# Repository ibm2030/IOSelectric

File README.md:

IOSelectric
===========

Arduino based serial interface for an IBM I/O Selectric typewriter/printer

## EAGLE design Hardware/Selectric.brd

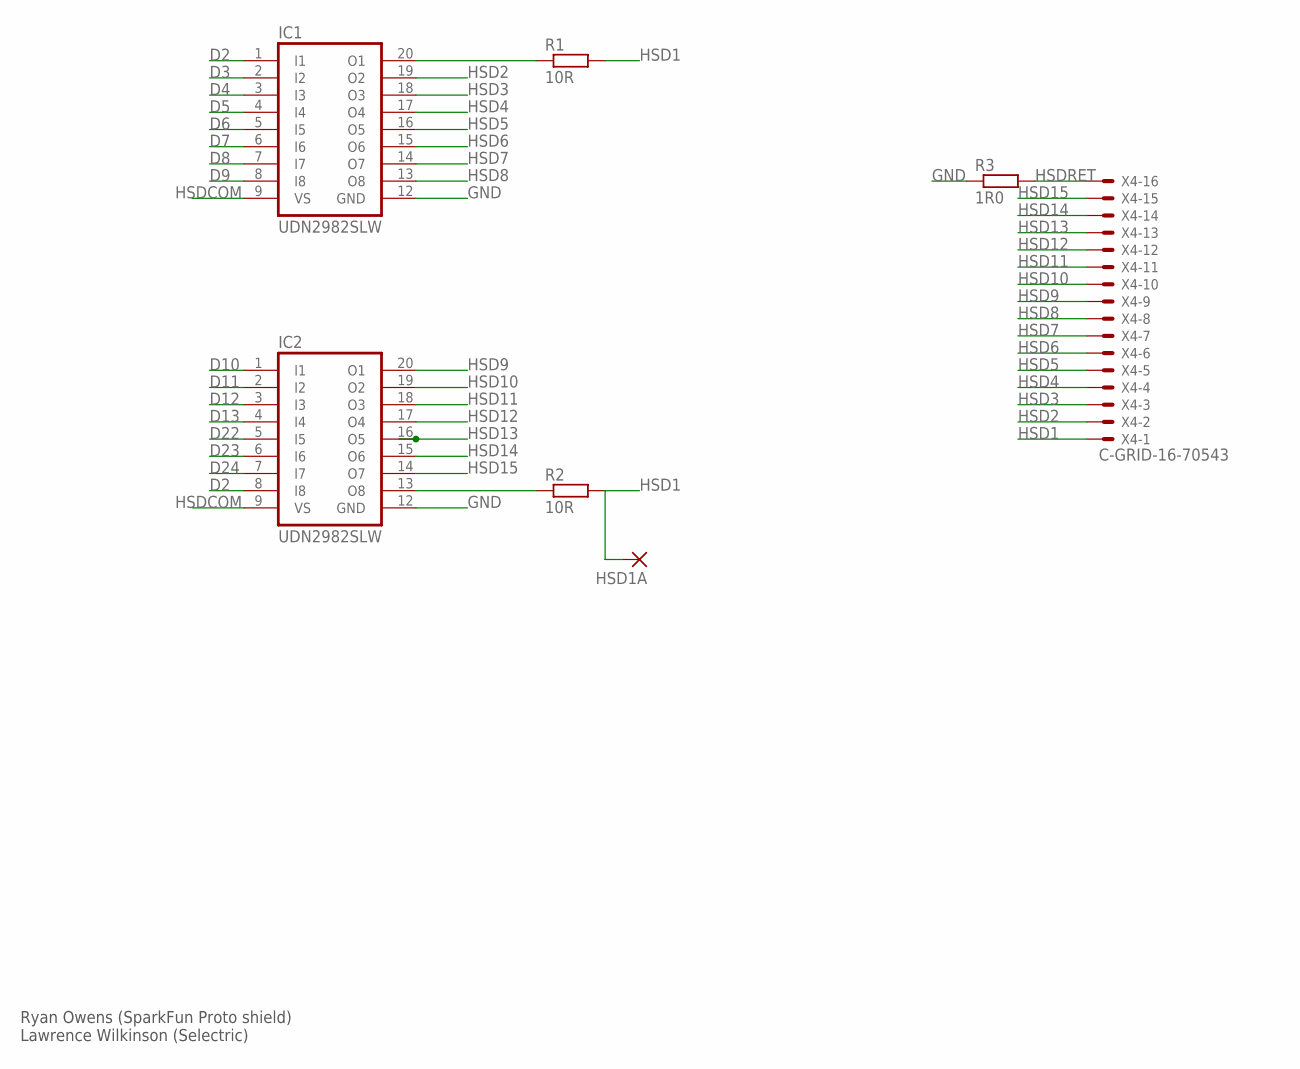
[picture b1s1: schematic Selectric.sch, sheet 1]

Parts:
HSD1A: 2,15/1,0
IC1, IC2: UDN2982SLW; SO20W; MPN UDN2982SLW
R1, R2: 10R; M1206
R3: 1R0; 0922/22
X4: C-GRID-16-70543; 70543-16

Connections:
D2: IC1.1 (I1), IC2.8 (I8); also elsewhere on the board
D3: IC1.2 (I2); also elsewhere on the board
D4: IC1.3 (I3); also elsewhere on the board
D5: IC1.4 (I4); also elsewhere on the board
D6: IC1.5 (I5); also elsewhere on the board
D7: IC1.6 (I6); also elsewhere on the board
D8: IC1.7 (I7); also elsewhere on the board
D9: IC1.8 (I8); also elsewhere on the board
D10: IC2.1 (I1); also elsewhere on the board
D11: IC2.2 (I2); also elsewhere on the board
D12: IC2.3 (I3); also elsewhere on the board
D13: IC2.4 (I4); also elsewhere on the board
D22: IC2.5 (I5); also elsewhere on the board
D23: IC2.6 (I6); also elsewhere on the board
D24: IC2.7 (I7); also elsewhere on the board
GND: IC1.12 (GND), IC2.12 (GND), R3.1; also elsewhere on the board
HSD1: HSD1A.1, R1.2, R2.2, X4.1
HSD1A: IC2.13 (O8), R2.1
HSD2: IC1.19 (O2), X4.2
HSD3: IC1.18 (O3), X4.3
HSD4: IC1.17 (O4), X4.4
HSD5: IC1.16 (O5), X4.5
HSD6: IC1.15 (O6), X4.6
HSD7: IC1.14 (O7), X4.7
HSD8: IC1.13 (O8), X4.8
HSD9: IC2.20 (O1), X4.9
HSD10: IC2.19 (O2), X4.10
HSD11: IC2.18 (O3), X4.11
HSD12: IC2.17 (O4), X4.12
HSD13: IC2.16 (O5), X4.13
HSD14: IC2.15 (O6), X4.14
HSD15: IC2.14 (O7), X4.15
HSDCOM: IC1.9 (VS), IC2.9 (VS); also elsewhere on the board
HSDRET: R3.2, X4.16; also elsewhere on the board
unnamed: IC1.20 (O1), R1.1

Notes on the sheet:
Ryan Owens (SparkFun Proto shield) Lawrence Wilkinson (Selectric)

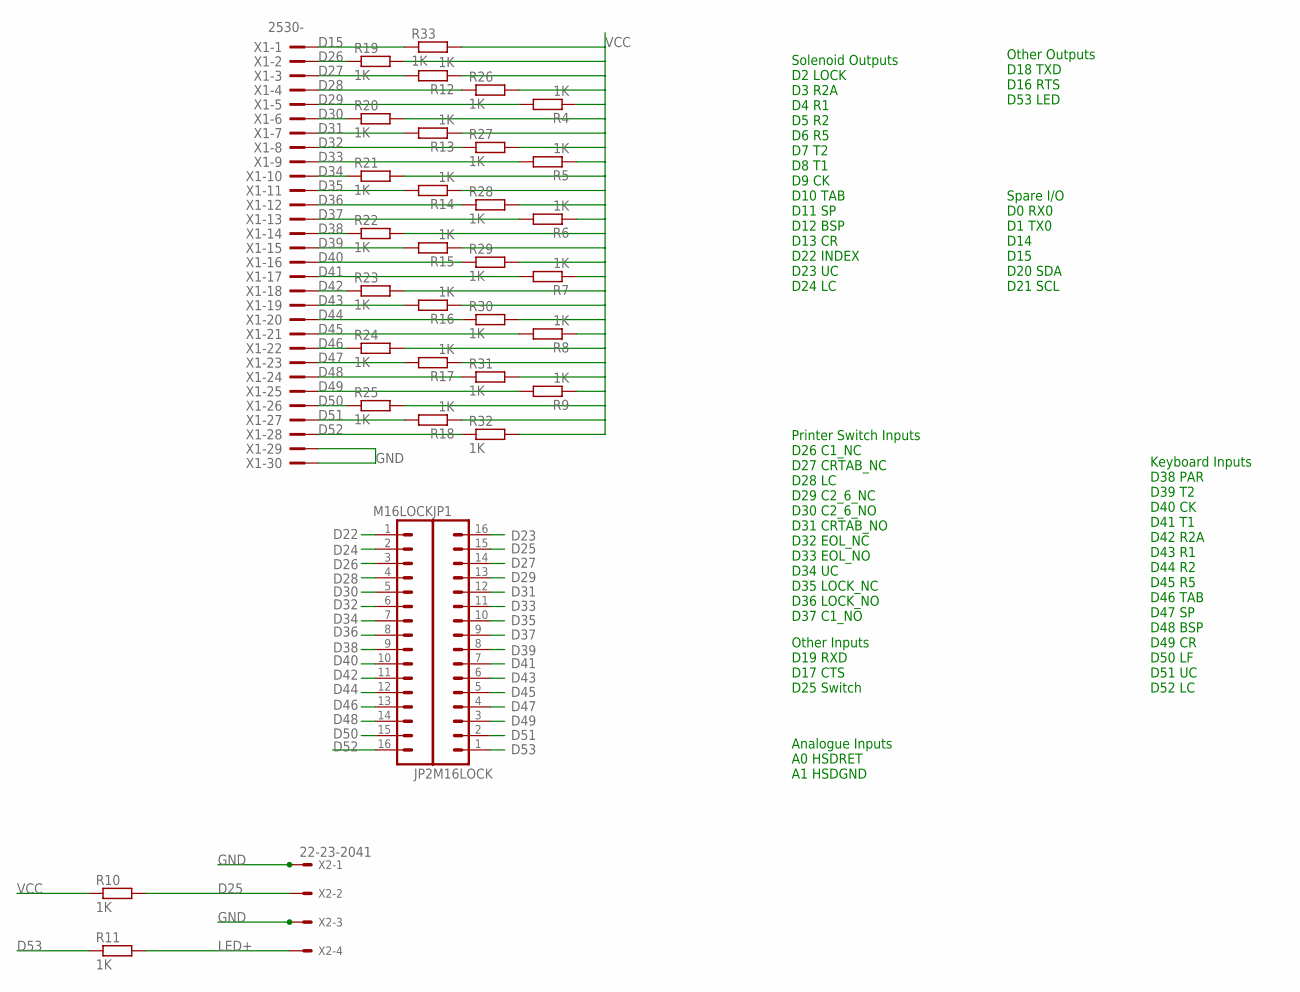
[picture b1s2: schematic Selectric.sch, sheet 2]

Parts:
JP1, JP2: M16LOCK; 1X16_LOCK; MPN 61301611121
R4, R5, R6, R7, R8, R9, R10, R11, R12, R13, R14, R15, R16, R17, R18, R19, R20, R21, R22, R23, R24, R25, R26, R27, R28, R29, R30, R31, R32, R33: 1K; M1206
X1: 2530-; PAK100/2500-30; MPN PAK100/2500-30
X2: 22-23-2041; MPN 280371-2

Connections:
D15: R33.1, X1.1; also elsewhere on the board
D22: JP2.1; also elsewhere on the board
D23: JP1.16; also elsewhere on the board
D24: JP2.2; also elsewhere on the board
D25: JP1.15, R10.2, X2.2
D26: JP2.3, R19.1, X1.2
D27: JP1.14, R12.2, X1.3
D28: JP2.4, R26.1, X1.4
D29: JP1.13, R4.2, X1.5
D30: JP2.5, R20.1, X1.6
D31: JP1.12, R13.2, X1.7
D32: JP2.6, R27.1, X1.8
D33: JP1.11, R5.2, X1.9
D34: JP2.7, R21.1, X1.10
D35: JP1.10, R14.2, X1.11
D36: JP2.8, R28.1, X1.12
D37: JP1.9, R6.2, X1.13
D38: JP2.9, R22.1, X1.14
D39: JP1.8, R15.2, X1.15
D40: JP2.10, R29.1, X1.16
D41: JP1.7, R7.2, X1.17
D42: JP2.11, R23.1, X1.18
D43: JP1.6, R16.2, X1.19
D44: JP2.12, R30.1, X1.20
D45: JP1.5, R8.2, X1.21
D46: JP2.13, R24.1, X1.22
D47: JP1.4, R17.2, X1.23
D48: JP2.14, R31.1, X1.24
D49: JP1.3, R9.2, X1.25
D50: JP2.15, R25.1, X1.26
D51: JP1.2, R18.2, X1.27
D52: JP2.16, R32.1, X1.28
D53: JP1.1, R11.1
GND: X1.29, X1.30, X2.1, X2.3; also elsewhere on the board
LED+: R11.2, X2.4
VCC: R4.1, R5.1, R6.1, R7.1, R8.1, R9.1, R10.1, R12.1, R13.1, R14.1, R15.1, R16.1, R17.1, R18.1, R19.2, R20.2, R21.2, R22.2, R23.2, R24.2, R25.2, R26.2, R27.2, R28.2, R29.2, R30.2, R31.2, R32.2, R33.2; also elsewhere on the board

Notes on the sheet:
Solenoid Outputs D2 LOCK D3 R2A D4 R1 D5 R2 D6 R5 D7 T2 D8 T1 D9 CK D10 TAB D11 SP D12 BSP D13 CR D22 INDEX D23 UC D24 LC
Other Outputs D18 TXD D16 RTS D53 LED
Printer Switch Inputs D26 C1_NC D27 CRTAB_NC D28 LC D29 C2_6_NC D30 C2_6_NO D31 CRTAB_NO D32 EOL_NC D33 EOL_NO D34 UC D35 LOCK_NC D36 LOCK_NO D37 C1_NO
Keyboard Inputs D38 PAR D39 T2 D40 CK D41 T1 D42 R2A D43 R1 D44 R2 D45 R5 D46 TAB D47 SP D48 BSP D49 CR D50 LF D51 UC D52 LC
Other Inputs D19 RXD D17 CTS D25 Switch
Analogue Inputs A0 HSDRET A1 HSDGND
Spare I/O D0 RX0 D1 TX0 D14 D15 D20 SDA D21 SCL

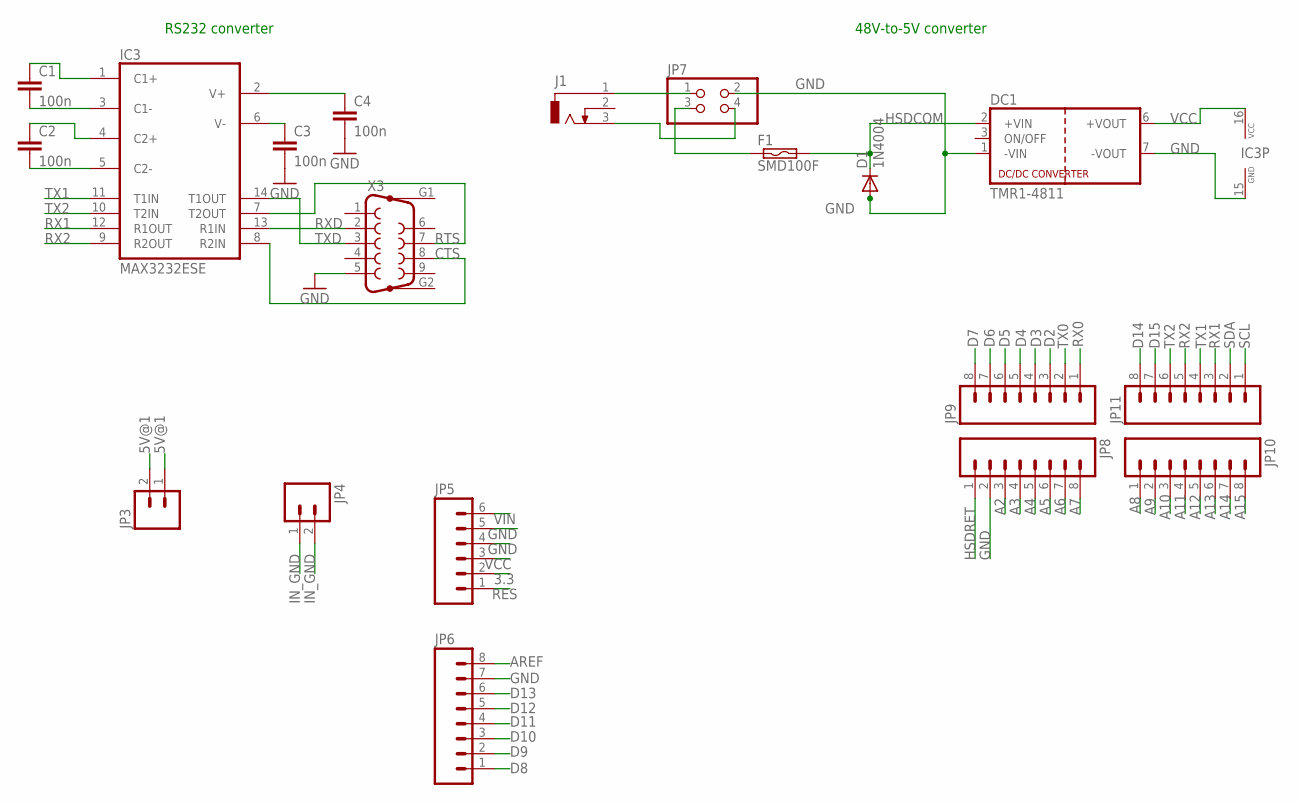
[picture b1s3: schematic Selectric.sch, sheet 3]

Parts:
C1, C2, C3, C4: 100n; C0603
D1: 1N4004; DO41-10
DC1: TMR1-4811; TRACO_SIP-8; MPN TMR1-4811
F1: SMD100F; SMD050F; MPN 3404.0009.11
IC3: MAX3232ESE; SO16; MPN MAX3232CSE
J1: DCJ0303
JP3, JP4: M02LOCK; 1X02_LOCK
JP5: M06LOCK; 1X06_LOCK; MPN 826629-6
JP6, JP8, JP9, JP10, JP11: M08LOCK; 1X08_LOCK; MPN 826629-8
JP7: PINHD-2X2; 2X02; MPN 826632-2
X3: F09HP; MPN FCE17-E09PA-490

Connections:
3.3: JP5.2
5V@1: JP3.1, JP3.2
A2: JP8.3
A3: JP8.4
A4: JP8.5
A5: JP8.6
A6: JP8.7
A7: JP8.8
A8: JP10.1
A9: JP10.2
A10: JP10.3
A11: JP10.4
A12: JP10.5
A13: JP10.6
A14: JP10.7
A15: JP10.8
AREF: JP6.8
CTS: IC3.8 (R2IN), X3.8
D2: JP9.3; also elsewhere on the board
D3: JP9.4; also elsewhere on the board
D4: JP9.5; also elsewhere on the board
D5: JP9.6; also elsewhere on the board
D6: JP9.7; also elsewhere on the board
D7: JP9.8; also elsewhere on the board
D8: JP6.1; also elsewhere on the board
D9: JP6.2; also elsewhere on the board
D10: JP6.3; also elsewhere on the board
D11: JP6.4; also elsewhere on the board
D12: JP6.5; also elsewhere on the board
D13: JP6.6; also elsewhere on the board
D14: JP11.8
D15: JP11.7; also elsewhere on the board
GND: C3.2, C4.2, D1.A, DC1.1 (-VIN), DC1.7 (-VOUT), IC3.15 (GND), JP5.4, JP5.5, JP6.7, JP7.2, JP8.2, X3.5; also elsewhere on the board
HSDCOM: D1.C, DC1.2 (+VIN), F1.2; also elsewhere on the board
HSDRET: JP8.1; also elsewhere on the board
IN_GND: JP4.1, JP4.2
unnamed: C1.1, IC3.1 (C1+)
unnamed: C2.1, IC3.4 (C2+)
unnamed: C1.2, IC3.3 (C1-)
unnamed: C2.2, IC3.5 (C2-)
unnamed: C4.1, IC3.2 (V+)
unnamed: C3.1, IC3.6 (V-)
unnamed: J1.3, JP7.4
unnamed: J1.1, JP7.1
unnamed: F1.1, JP7.3
RES: JP5.1
RTS: IC3.7 (T2OUT), X3.7
RX0: JP9.1
RX1: IC3.12 (R1OUT), JP11.3
RX2: IC3.9 (R2OUT), JP11.5
RXD: IC3.13 (R1IN), X3.2
SCL: JP11.1
SDA: JP11.2
TX0: JP9.2
TX1: IC3.11 (T1IN), JP11.4
TX2: IC3.10 (T2IN), JP11.6
TXD: IC3.14 (T1OUT), X3.3
VCC: DC1.6 (+VOUT), IC3.16 (VCC), JP5.3; also elsewhere on the board
VIN: JP5.6

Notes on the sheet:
48V-to-5V converter
RS232 converter

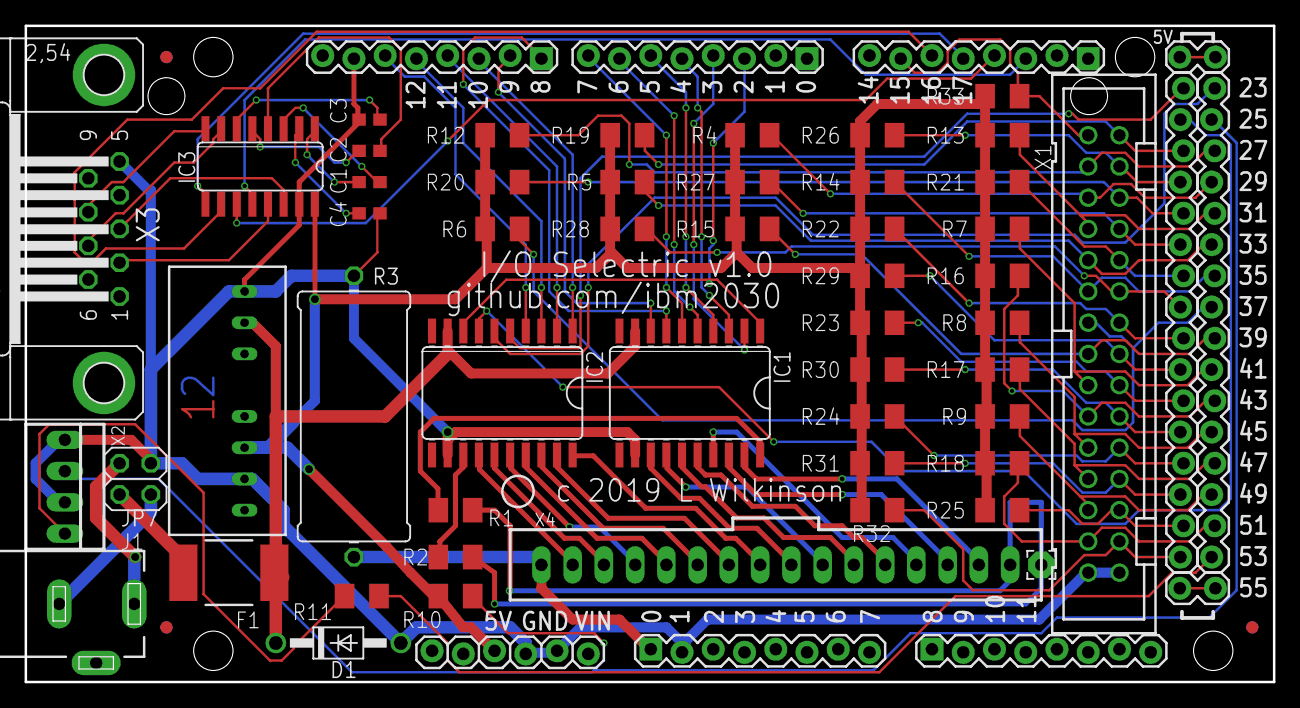
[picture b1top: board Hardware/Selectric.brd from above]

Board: 2 copper layers, 101.5 x 53.3 mm, 63 parts (0 on the bottom side), 86 nets.

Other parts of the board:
U$1, U$2, U$3: CIRCLE-1MM-3R

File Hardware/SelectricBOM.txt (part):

Partlist exported from /home/ljw/Documents/eagle/Selectric/Selectric.sch at 2/06/19 10:50 PM

Part Value           Device          Package        Description                                      MF              MPN             OC_FARNELL OC_NEWARK
C1   100n            C-EUC0603       C0603          CAPACITOR, European symbol                                                                           
C2   100n            C-EUC0603       C0603          CAPACITOR, European symbol                                                                           
C3   100n            C-EUC0603       C0603          CAPACITOR, European symbol                                                                           
C4   100n            C-EUC0603       C0603          CAPACITOR, European symbol                                                                           
D1   1N4004          1N4004          DO41-10        DIODE                                                                                                
DC1  TMR1-4811       TMR1-4811       TRACO_SIP-8                                                     TRACO           TMR1-4811                           
F1   SMD100F         SMD100F         SMD050F        PolySwitch (TM) Resettable Device                Schurter        3404.0009.11                        
IC1  UDN2982SLW      UDN2982SLW      SO20W          DRIVER ARRAY                                     Allegro         UDN2982SLW                          
IC2  UDN2982SLW      UDN2982SLW      SO20W          DRIVER ARRAY                                     Allegro         UDN2982SLW                          
IC3  MAX3232ESE      MAX3232ESE      SO16           True RS-232 Transceivers 3.0V to 5.5V, Low-Power MAXIM           MAX3232ESE      9725539    79C3880  
J1                   DCJ0303         DCJ0303        DC POWER JACK                                                                    unknown    unknown  
JP1  M16LOCK         M16LOCK         1X16_LOCK                                                       WURTH           61301611121                         
JP2  M16LOCK         M16LOCK         1X16_LOCK                                                       WURTH           61301611121                         
JP3                  M02LOCK         1X02_LOCK      Header 2                                                                                             
JP4                  M02LOCK         1X02_LOCK      Header 2                                                                                             
JP5                  M06LOCK         1X06_LOCK      Header 6                                         TE CONNECTIVITY 826629-6                            
JP6                  M08LOCK         1X08_LOCK      Header 8                                         TE CONNECTIVITY 826629-8                            
JP7                  PINHD-2X2       2X02           PIN HEADER                                       TE CONNECTIVITY 826632-2                            
JP8                  M08LOCK         1X08_LOCK      Header 8                                         TE CONNECTIVITY 826629-8                            
JP9                  M08LOCK         1X08_LOCK      Header 8                                         TE CONNECTIVITY 826629-8                            
JP10                 M08LOCK         1X08_LOCK      Header 8                                         TE CONNECTIVITY 826629-8                            
JP11                 M08LOCK         1X08_LOCK      Header 8                                         TE CONNECTIVITY 826629-8                            
R1   10R             R-EU_M1206      M1206          RESISTOR, European symbol                                                                            
R2   10R             R-EU_M1206      M1206          RESISTOR, European symbol                                                                            
R3   1R0             R-EU_0922/22    0922/22        RESISTOR, European symbol                                                                            
R4   1K              R-EU_M1206      M1206          RESISTOR, European symbol                                                                            
R5   1K              R-EU_M1206      M1206          RESISTOR, European symbol                                                                            
R6   1K              R-EU_M1206      M1206          RESISTOR, European symbol                                                                            
R7   1K              R-EU_M1206      M1206          RESISTOR, European symbol                                                                            
R8   1K              R-EU_M1206      M1206          RESISTOR, European symbol                                                                            
R9   1K              R-EU_M1206      M1206          RESISTOR, European symbol                                                                            
R10  1K              R-EU_M1206      M1206          RESISTOR, European symbol                                                                            
R11  1K              R-EU_M1206      M1206          RESISTOR, European symbol                                                                            
R12  1K              R-EU_M1206      M1206          RESISTOR, European symbol                                                                            
R13  1K              R-EU_M1206      M1206          RESISTOR, European symbol                                                                            
R14  1K              R-EU_M1206      M1206          RESISTOR, European symbol                                                                            
R15  1K              R-EU_M1206      M1206          RESISTOR, European symbol                                                                            
R16  1K              R-EU_M1206      M1206          RESISTOR, European symbol                                                                            
R17  1K              R-EU_M1206      M1206          RESISTOR, European symbol                                                                            
R18  1K              R-EU_M1206      M1206          RESISTOR, European symbol                                                                            
R19  1K              R-EU_M1206      M1206          RESISTOR, European symbol                                                                            
R20  1K              R-EU_M1206      M1206          RESISTOR, European symbol                                                                            
R21  1K              R-EU_M1206      M1206          RESISTOR, European symbol                                                                            
R22  1K              R-EU_M1206      M1206          RESISTOR, European symbol                                                                            
R23  1K              R-EU_M1206      M1206          RESISTOR, European symbol                                                                            
R24  1K              R-EU_M1206      M1206          RESISTOR, European symbol                                                                            
R25  1K              R-EU_M1206      M1206          RESISTOR, European symbol                                                                            
R26  1K              R-EU_M1206      M1206          RESISTOR, European symbol                                                                            
R27  1K              R-EU_M1206      M1206          RESISTOR, European symbol                                                                            
R28  1K              R-EU_M1206      M1206          RESISTOR, European symbol                                                                            
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
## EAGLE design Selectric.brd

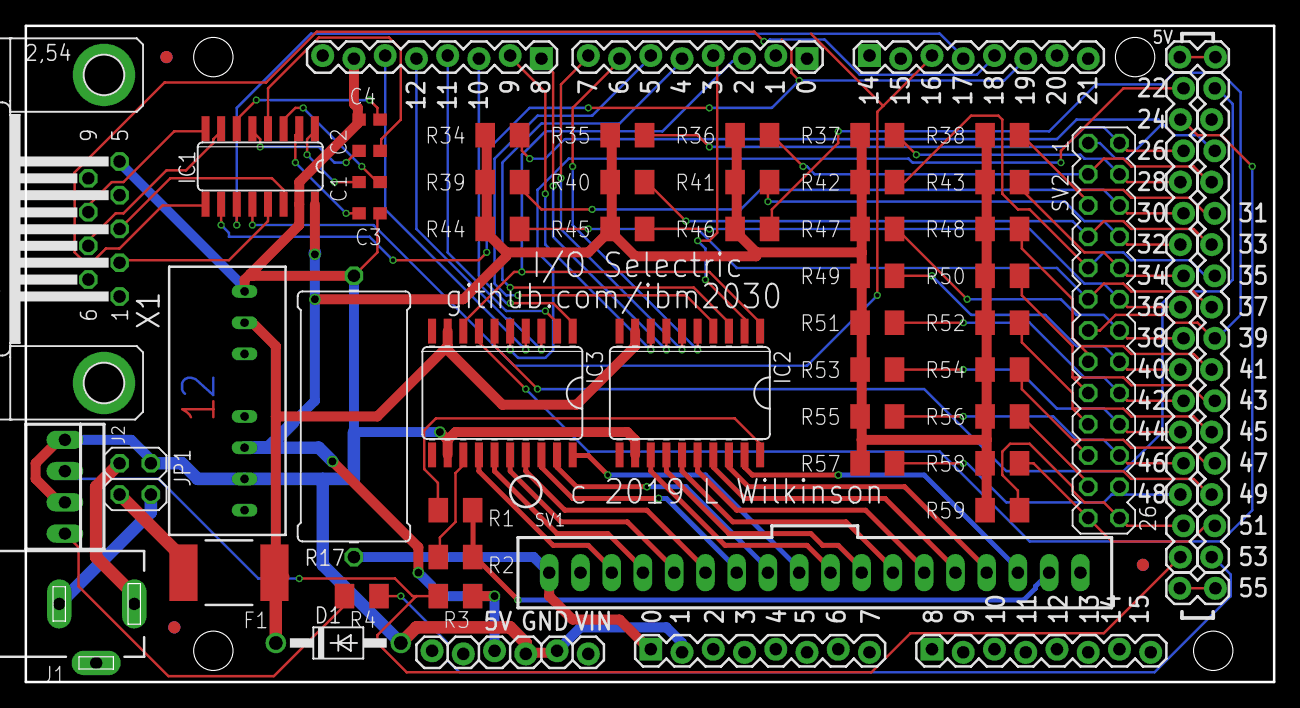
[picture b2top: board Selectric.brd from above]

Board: 2 copper layers, 101.5 x 53.3 mm, 60 parts (0 on the bottom side), 84 nets.

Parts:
C1, C2, C3, C4: 100n; C0603
D1: 1N4004; DO41-10
DC1: TMR; TRACO_SIP-8
F1: SMD100F; SMD050F
IC1: MAX3232ESE; SO16
IC2, IC3: UDN2982SLW; SO20W
J1: DCJ0303
J2: 22-23-2041
JP1: 2X02
JP3, JP4, JP5, JP6, JP7: 1X08_LOCK
JP8, JP9: M16LOCK; 1X16_LOCK
JP10: 1X06_LOCK
JP11, JP12: 1X02_LOCK
R1, R2: 10R; M1206
R3, R4, R34, R35, R36, R37, R38, R39, R40, R41, R42, R43, R44, R45, R46, R47, R48, R49, R50, R51, R52, R53, R54, R55, R56, R57, R58, R59: 220R; M1206
R17: 1R0; 0922/22
SV1: C-GRID-18-70543; 70543-18
SV2: MA13-2
U$1, U$2, U$3: CIRCLE-1MM-3R
X1: F09HP

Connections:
5V@1: JP12.1, JP12.2
CTS: IC1.8, X1.8
D2: IC2.1, IC3.8, JP4.3
D3: IC2.2, JP4.4
D4: IC2.3, JP4.5
D5: IC2.4, JP4.6
D6: IC2.5, JP4.7
D7: IC2.6, JP4.8
D8: IC2.7, JP3.1
D9: IC2.8, JP3.2
D10: IC3.1, JP3.3
D11: IC3.2, JP3.4
D12: IC3.3, JP3.5
D13: IC3.4, JP3.6
D22: IC3.5, JP9.1
D23: IC3.6, JP8.16
D24: IC3.7, JP9.2
D26: JP9.3, R35.1, SV2.2
D27: JP8.14, R34.2, SV2.1
D28: JP9.4, R37.1, SV2.4
D29: JP8.13, R36.2, SV2.3
D30: JP9.5, R39.1, SV2.6
D31: JP8.12, R38.2, SV2.5
D32: JP9.6, R41.1, SV2.8
D33: JP8.11, R40.2, SV2.7
D34: JP9.7, R43.1, SV2.10
D35: JP8.10, R42.2, SV2.9
D36: JP9.8, R45.1, SV2.12
D37: JP8.9, R44.2, SV2.11
D38: JP9.9, R47.1, SV2.14
D39: JP8.8, R46.2, SV2.13
D40: JP9.10, R49.1, SV2.16
D41: JP8.7, R48.2, SV2.15
D42: JP9.11, R51.1, SV2.18
D43: JP8.6, R50.2, SV2.17
D44: JP9.12, R53.1, SV2.20
D45: JP8.5, R52.2, SV2.19
D46: JP9.13, R55.1, SV2.22
D47: JP8.4, R54.2, SV2.21
D48: JP9.14, R57.1, SV2.24
D49: JP8.3, R56.2, SV2.23
D50: JP9.15, R59.1, SV2.26
D51: JP8.2, R58.2, SV2.25
D52: J2.2, JP9.16, R3.2
D53: JP8.1, R4.1
GND: C3.2, C4.2, D1.A, DC1.1, DC1.7, IC1.15, IC2.12, IC3.12, J2.1, J2.3, JP1.2, JP3.7, JP7.2, JP10.4, JP10.5, R17.1, X1.5
HSD1: R1.2, R2.2, SV1.2
HSD2: IC2.19, SV1.3
HSD3: IC2.18, SV1.4
HSD4: IC2.17, SV1.5
HSD5: IC2.16, SV1.6
HSD6: IC2.15, SV1.7
HSD7: IC2.14, SV1.8
HSD8: IC2.13, SV1.9
HSD9: IC3.20, SV1.10
HSD10: IC3.19, SV1.11
HSD11: IC3.18, SV1.12
HSD12: IC3.17, SV1.13
HSD13: IC3.16, SV1.14
HSD14: IC3.15, SV1.15
HSD15: IC3.14, SV1.16
HSDCOM: D1.C, DC1.2, F1.2, IC2.9, IC3.9
HSDRET: JP7.1, R17.2, SV1.18
IN_GND: JP11.1, JP11.2
LED+: J2.4, R4.2
unnamed: C1.1, IC1.1
unnamed: C2.1, IC1.4
unnamed: C1.2, IC1.3
unnamed: C2.2, IC1.5
unnamed: IC3.13, R2.1
unnamed: C3.1, IC1.2
unnamed: C4.1, IC1.6
unnamed: IC2.20, R1.1
unnamed: J1.3, JP1.4
unnamed: J1.1, JP1.1
unnamed: F1.1, JP1.3
RTS: IC1.7, X1.7
RX1: IC1.12, JP5.3
RX2: IC1.9, JP5.5
RXD: IC1.13, X1.2
TX1: IC1.11, JP5.4
TX2: IC1.10, JP5.6
TXD: IC1.14, X1.3
VCC: DC1.6, IC1.16, JP10.3, R3.1, R34.1, R35.2, R36.1, R37.2, R38.1, R39.2, R40.1, R41.2, R42.1, R43.2, R44.1, R45.2, R46.1, R47.2, R48.1, R49.2, R50.1, R51.2, R52.1, R53.2, R54.1, R55.2, R56.1, R57.2, R58.1, R59.2

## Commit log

2013-03-03 Start Software project
2013-03-03 Start Hardware project
2013-03-03 Create Hardware directory
2013-03-16 Initial version of Arduino program
2013-03-16 Move .ino to IOSelectric project directory
2013-03-19 V1.1 Re-work to remove String objects Add Min/Max times to statistics Remove superfluous debugging printlns Fix various timeouts and stat calcs Add check for previous cycle complete at start of print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
2013-03-23 V1.2 Tidy up timeouts Fix up correspondence coding table Add cycle time stats Add XON/XOFF and CTS/RTS handshaking
2013-06-12 Add keyboard support
2013-07-10 Tidy up timeouts for real Selectric Select appropriate options for use with S/360 emulator Prevent CR from terminating too early Fix bug in CR stats, add CONTACT_ definitions Allow correct keyboard o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
2013-07-10 IBM 360 assembler program to demonstrate I/O Selectric operation The program waits for a line to be typed, the prints a prompt Four lines of up to 20 characters can be typed, which will then be print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
2014-02-01 Add temporary pdf schematic of Arduino interface
2019-04-29 Add files via upload
    Initial 2-layer version, not checked.
    DRU file is eC_2Layer_PClass6_BaseCopperO18_eCDefault.dru from https://www.eurocircuits.com/EAGLE-DRU-files-for-the-Eurocircuits-pooling-services/
2019-04-29 Delete Selectric.pdf
    Replaced by SelectricSCH.pdf
2019-05-08 Updated schematic and tidied board
    Added Arduino 5V power feed. Tidied some traces and labels.
2019-05-12 Adjust some screen labels for tidiness
2019-05-14 Modify to use Allegro A2982SLW-T drivers
    Replace discrete mosfets with A2982 driver ICs.
2019-05-14 Images of PCB
2019-05-26 Add switch/LED header J2
2019-05-27 Finalise components and values. add BoM
2019-06-02 Modify connectors, assign I/Os
    Add eC-stencil registration holes
2019-06-02 Board images for latest update
2019-06-08 Version as ordered
    Note BoM is not necessarily accurate
2019-06-08 Assign Input and Output numbers to match PCB
    Note PCB has two drivers for the LOCK output driven from the D2 output. These can be separated at the power side by cutting a trace but will still be driven from D2 unless further modifications are m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
2025-12-16 Fix critical logic error in shift checking
    Fixed bug in printCharacter() where the shift check condition used OR (||)
    instead of AND (&&), causing it to always evaluate to true. This resulted in
    unnecessary shift operations even for characters like "." and "," that exist
    on both shift levels.
    Changed line 740 from:
    if ((code!=0x1a)|| (code!=0x29))
2025-12-16 Make Claude-recommended fixes
